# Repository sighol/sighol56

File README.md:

udev rules
==========

copy the udev rule into /etc/udev/rules.d

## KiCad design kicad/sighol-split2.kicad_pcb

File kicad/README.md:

# Sighol56

My first split keyboard using [RP2040 zero](https://www.waveshare.com/wiki/RP2040-Zero) as the
microcontroller.

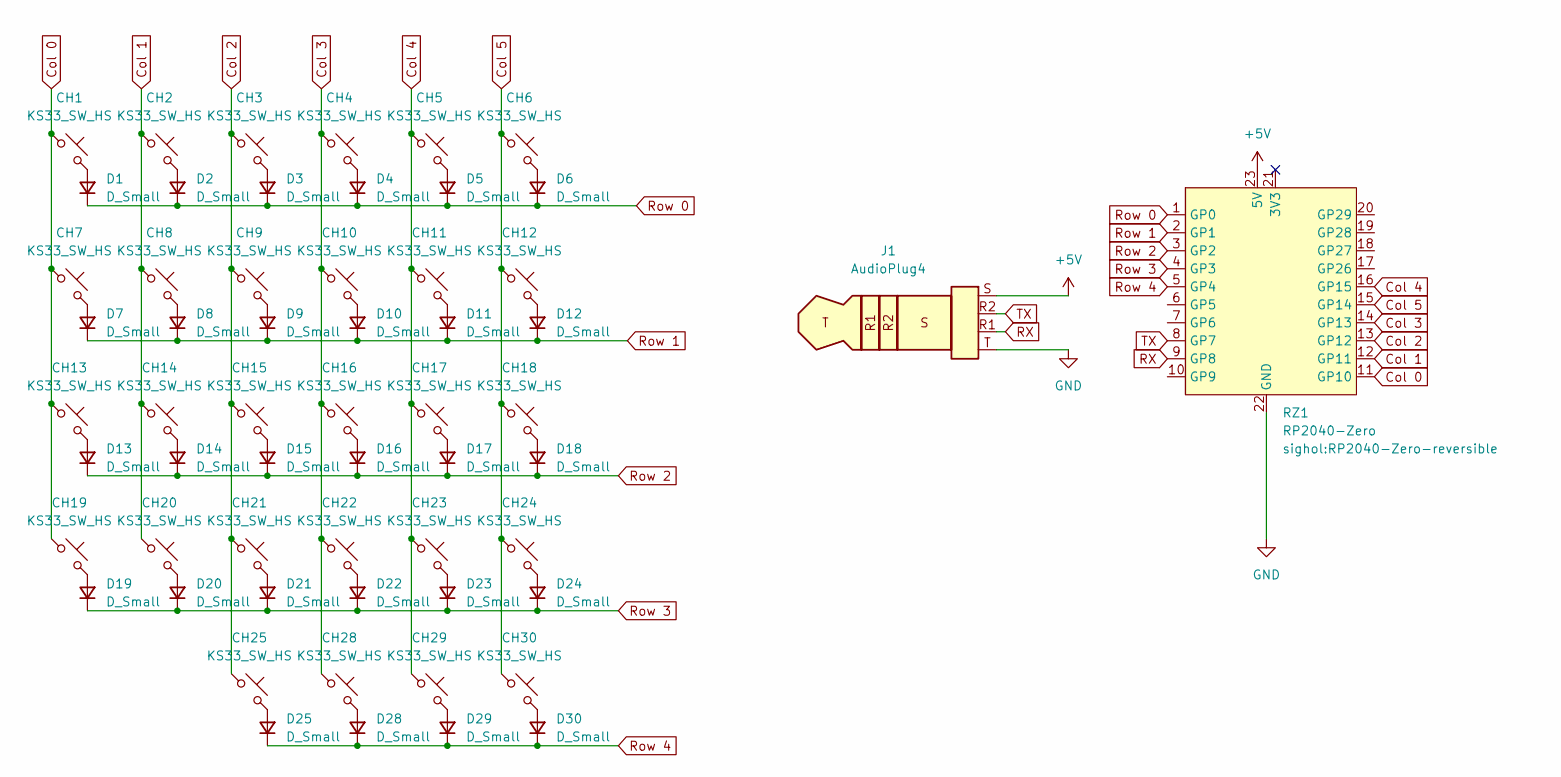
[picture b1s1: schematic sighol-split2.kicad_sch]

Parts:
CH1, CH2, CH3, CH4, CH5, CH6, CH7, CH8, CH9, CH10, CH11, CH12, CH13, CH14, CH15, CH16, CH17, CH18, CH19, CH20, CH21, CH22, CH23, CH24, CH25, CH28, CH29, CH30: KS33_SW_HS; Kailh_socket_PG1350_optional_reversible_clean
D1, D2, D3, D4, D5, D6, D7, D8, D9, D10, D11, D12, D13, D14, D15, D16, D17, D18, D19, D20, D21, D22, D23, D24, D25, D28, D29, D30: D_Small; D_DO-35_SOD27_P7.62mm_Horizontal
J1: AudioPlug4; TRRS-PJ-320A
RZ1: RP2040-Zero; RP2040-Zero-reversible

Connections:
+5V: J1.S, RZ1.23 (5V)
Col 0: CH1.1, CH7.1, CH13.1, CH19.1, RZ1.11 (GP10)
Col 1: CH2.1, CH8.1, CH14.1, CH20.1, RZ1.12 (GP11)
Col 2: CH3.1, CH9.1, CH15.1, CH21.1, CH25.1, RZ1.13 (GP12)
Col 3: CH4.1, CH10.1, CH16.1, CH22.1, CH28.1, RZ1.14 (GP13)
Col 4: CH5.1, CH11.1, CH17.1, CH23.1, CH29.1, RZ1.16 (GP15)
Col 5: CH6.1, CH12.1, CH18.1, CH24.1, CH30.1, RZ1.15 (GP14)
GND: J1.T, RZ1.22 (GND)
unnamed: CH1.2, D1.2 (A)
unnamed: CH2.2, D2.2 (A)
unnamed: CH3.2, D3.2 (A)
unnamed: CH4.2, D4.2 (A)
unnamed: CH5.2, D5.2 (A)
unnamed: CH6.2, D6.2 (A)
unnamed: CH7.2, D7.2 (A)
unnamed: CH8.2, D8.2 (A)
unnamed: CH9.2, D9.2 (A)
unnamed: CH10.2, D10.2 (A)
unnamed: CH11.2, D11.2 (A)
unnamed: CH12.2, D12.2 (A)
unnamed: CH13.2, D13.2 (A)
unnamed: CH14.2, D14.2 (A)
unnamed: CH15.2, D15.2 (A)
unnamed: CH16.2, D16.2 (A)
unnamed: CH17.2, D17.2 (A)
unnamed: CH18.2, D18.2 (A)
unnamed: CH19.2, D19.2 (A)
unnamed: CH20.2, D20.2 (A)
unnamed: CH21.2, D21.2 (A)
unnamed: CH22.2, D22.2 (A)
unnamed: CH23.2, D23.2 (A)
unnamed: CH24.2, D24.2 (A)
unnamed: CH25.2, D25.2 (A)
unnamed: CH28.2, D28.2 (A)
unnamed: CH29.2, D29.2 (A)
unnamed: CH30.2, D30.2 (A)
RX: J1.R1, RZ1.9 (GP8)
Row 0: D1.1 (K), D2.1 (K), D3.1 (K), D4.1 (K), D5.1 (K), D6.1 (K), RZ1.1 (GP0)
Row 1: D7.1 (K), D8.1 (K), D9.1 (K), D10.1 (K), D11.1 (K), D12.1 (K), RZ1.2 (GP1)
Row 2: D13.1 (K), D14.1 (K), D15.1 (K), D16.1 (K), D17.1 (K), D18.1 (K), RZ1.3 (GP2)
Row 3: D19.1 (K), D20.1 (K), D21.1 (K), D22.1 (K), D23.1 (K), D24.1 (K), RZ1.4 (GP3)
Row 4: D25.1 (K), D28.1 (K), D29.1 (K), D30.1 (K), RZ1.5 (GP4)
TX: J1.R2, RZ1.8 (GP7)

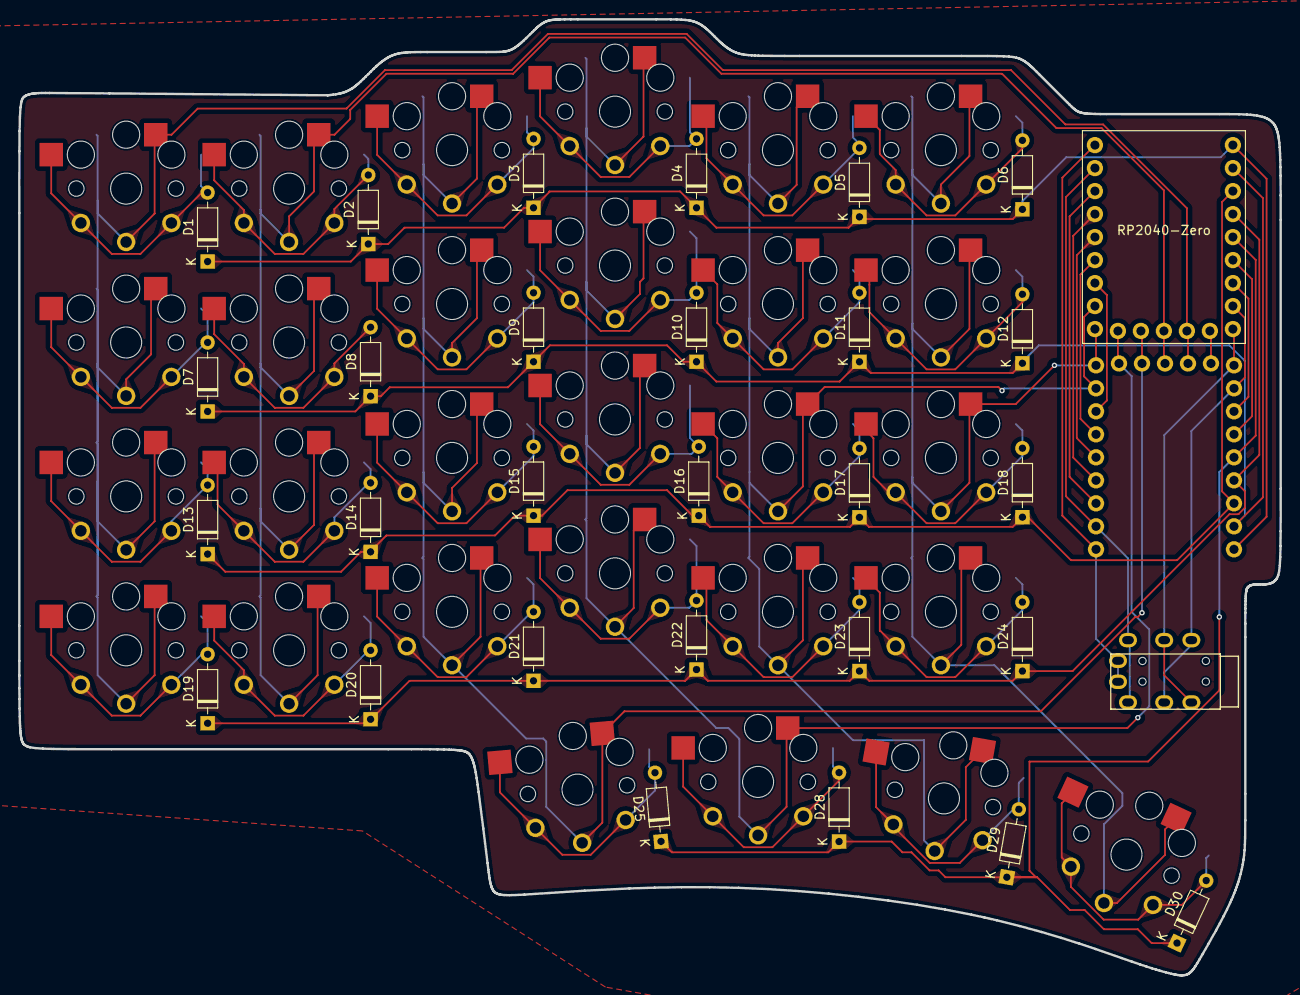
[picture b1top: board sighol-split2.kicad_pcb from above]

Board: 2 copper layers, 139.3 x 105.6 mm, 58 parts (0 on the bottom side), 43 nets.

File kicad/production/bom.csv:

Designator,Footprint,Quantity,Value,LCSC Part #
"CH1, CH10, CH11, CH12, CH13, CH14, CH15, CH16, CH17, CH18, CH19, CH2, CH20, CH21, CH22, CH23, CH24, CH25, CH28, CH29, CH3, CH30, CH4, CH5, CH6, CH7, CH8, CH9",Kailh_socket_PG1350_optional_reversible_clean,28,KS33_SW_HS,
"D1, D10, D11, D12, D13, D14, D15, D16, D17, D18, D19, D2, D20, D21, D22, D23, D24, D25, D28, D29, D3, D30, D4, D5, D6, D7, D8, D9",D_DO-35_SOD27_P7.62mm_Horizontal,28,D_Small,
J1,TRRS-PJ-320A,1,AudioPlug4,
RZ1,RP2040-Zero-reversible,1,RP2040-Zero,

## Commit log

2024-04-24 add settings layer
2024-04-24 Add left krokodille-sak
2024-04-25 Add all missing keys
2024-04-27 more changes
2024-04-30 print screen and kc_del
2024-04-30 Some XX's and a single quote on the right
2024-05-02 Double quote on Nav+O and move KC_O to a
2024-05-02 Add XXXXXXX on settings layer
2024-05-02 More X's
2024-05-02 Remove redundant comment in rules.mk
2024-05-27 html tag brackets
2024-05-28 Mouse keys
2024-06-06 Fix overview
2024-06-06 Rename layer names
2024-06-06 Fix mouse button
2024-06-09 Esc on rhs
2024-06-16 keybinding alignment (no changes)
2024-06-17 Add SPLIT_WATCHDOG_ENABLE
2024-06-17 Remove MASTER_LEFT: It is not in use
2024-06-17 Remove SPLIT_WATCHDOG_ENABLED, which caused the right hand to not work anymore
2024-06-20 BASE_MOD_TAP
2024-07-30 Add UUID on a key
2024-07-30 Add uuid.h
2024-07-30 SH_TIME and fix snprintf
2024-07-30 Both shifts turn on caps lock for one word
2024-07-30 console enabled + colemak_hex_transform
2024-07-30 fixup! console enabled + colemak_hex_transform
2024-07-30 proper uptime
2024-08-11 udev rule for mounting + formatting
2024-08-11 Better Makefile
2024-08-11 formatting
2024-08-11 Make uuid more random
2024-08-11 Add keyboard.json
2024-08-11 add slash on nav+w
2024-08-11 script that install udev rules and reloads
2024-08-17 KC_MINUS on left nav layer
2024-08-19 Volume on mouse layer
2024-08-19 Move KC_MINUS
2024-08-28 Make the seed more random
2024-09-24 colors?
2024-10-02 colors
2024-12-16 Put KC_DOT on numeric layer
2025-02-11 I think this is what I sent to production for my first split keyboard (sighol56)
2025-02-11 README.md
2025-02-11 Alignment
2025-02-25 Default mod tap
2025-02-25 Remove HMR on left index
2025-02-25 Disable quick tap
2025-05-02 Use combo instead of home-row-mods
2025-10-31 Use home-row-mods with chordal instead of combo again
2025-10-31 @ and $
2025-11-20 Allow ,.- while holding down n
2026-02-17 Fix send_string_rewrite and add reviewable button
2026-02-17 Add send_string_rewrite.h
2026-02-20 Remove no-mod-tap layer and add mod tap to colemak layer
2026-03-27 Add debounce to reduce chance of writing the i key twice
